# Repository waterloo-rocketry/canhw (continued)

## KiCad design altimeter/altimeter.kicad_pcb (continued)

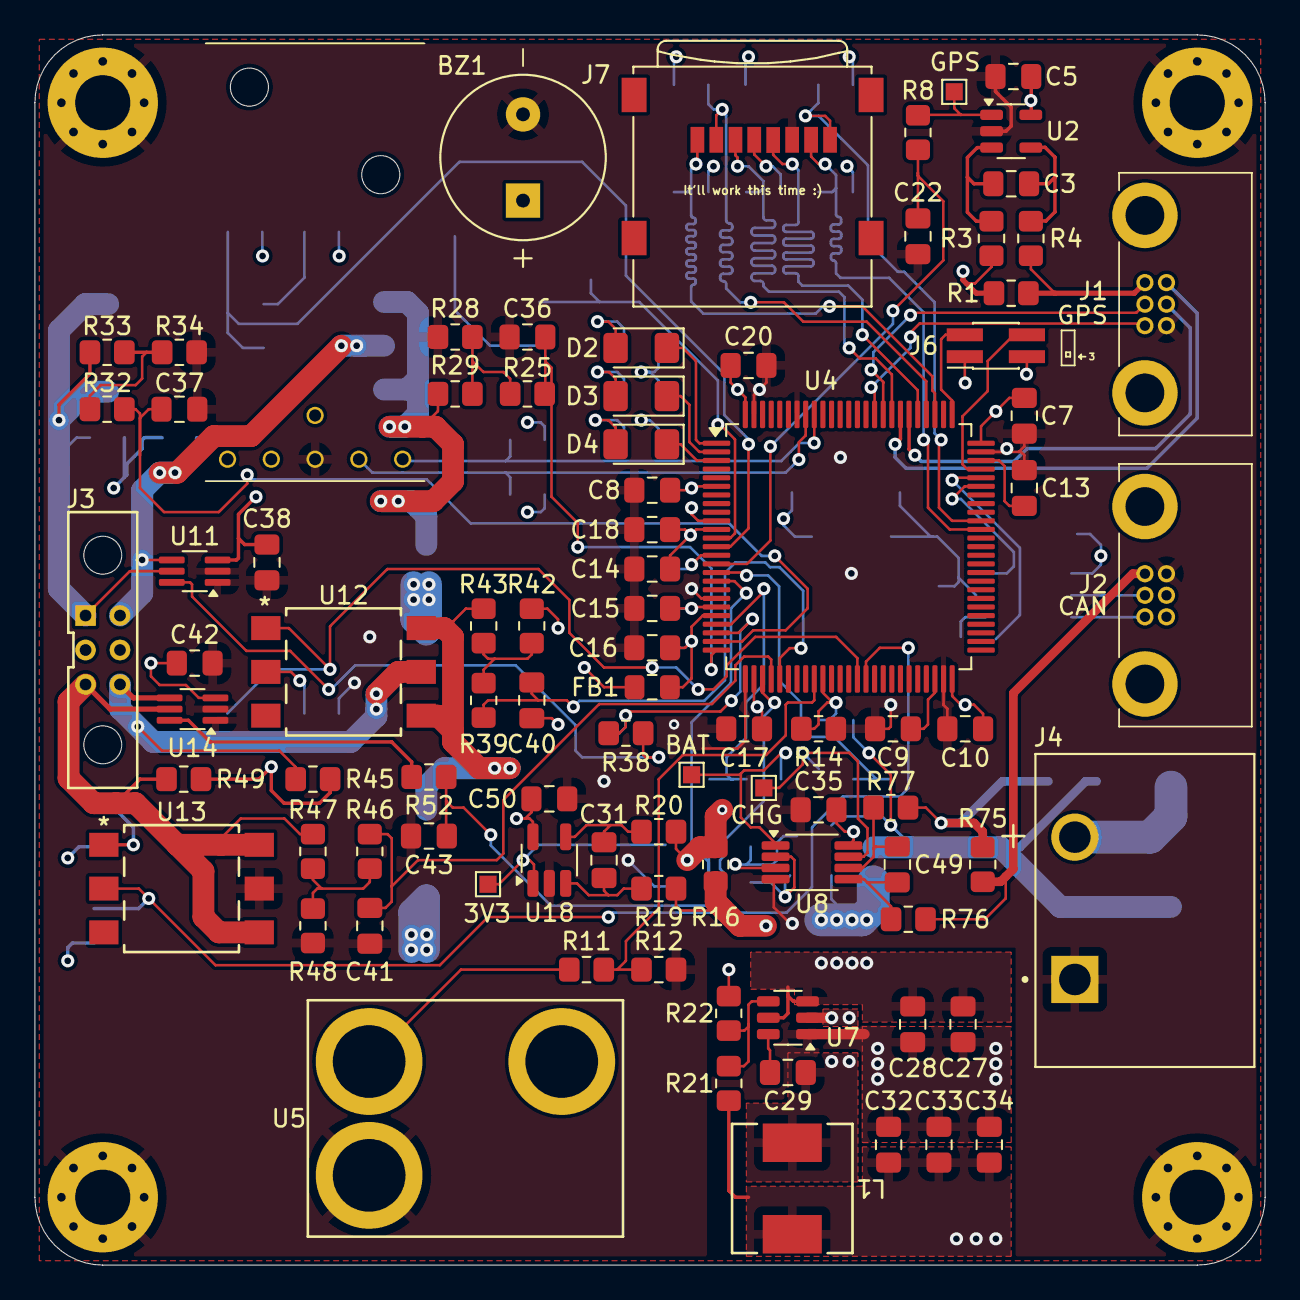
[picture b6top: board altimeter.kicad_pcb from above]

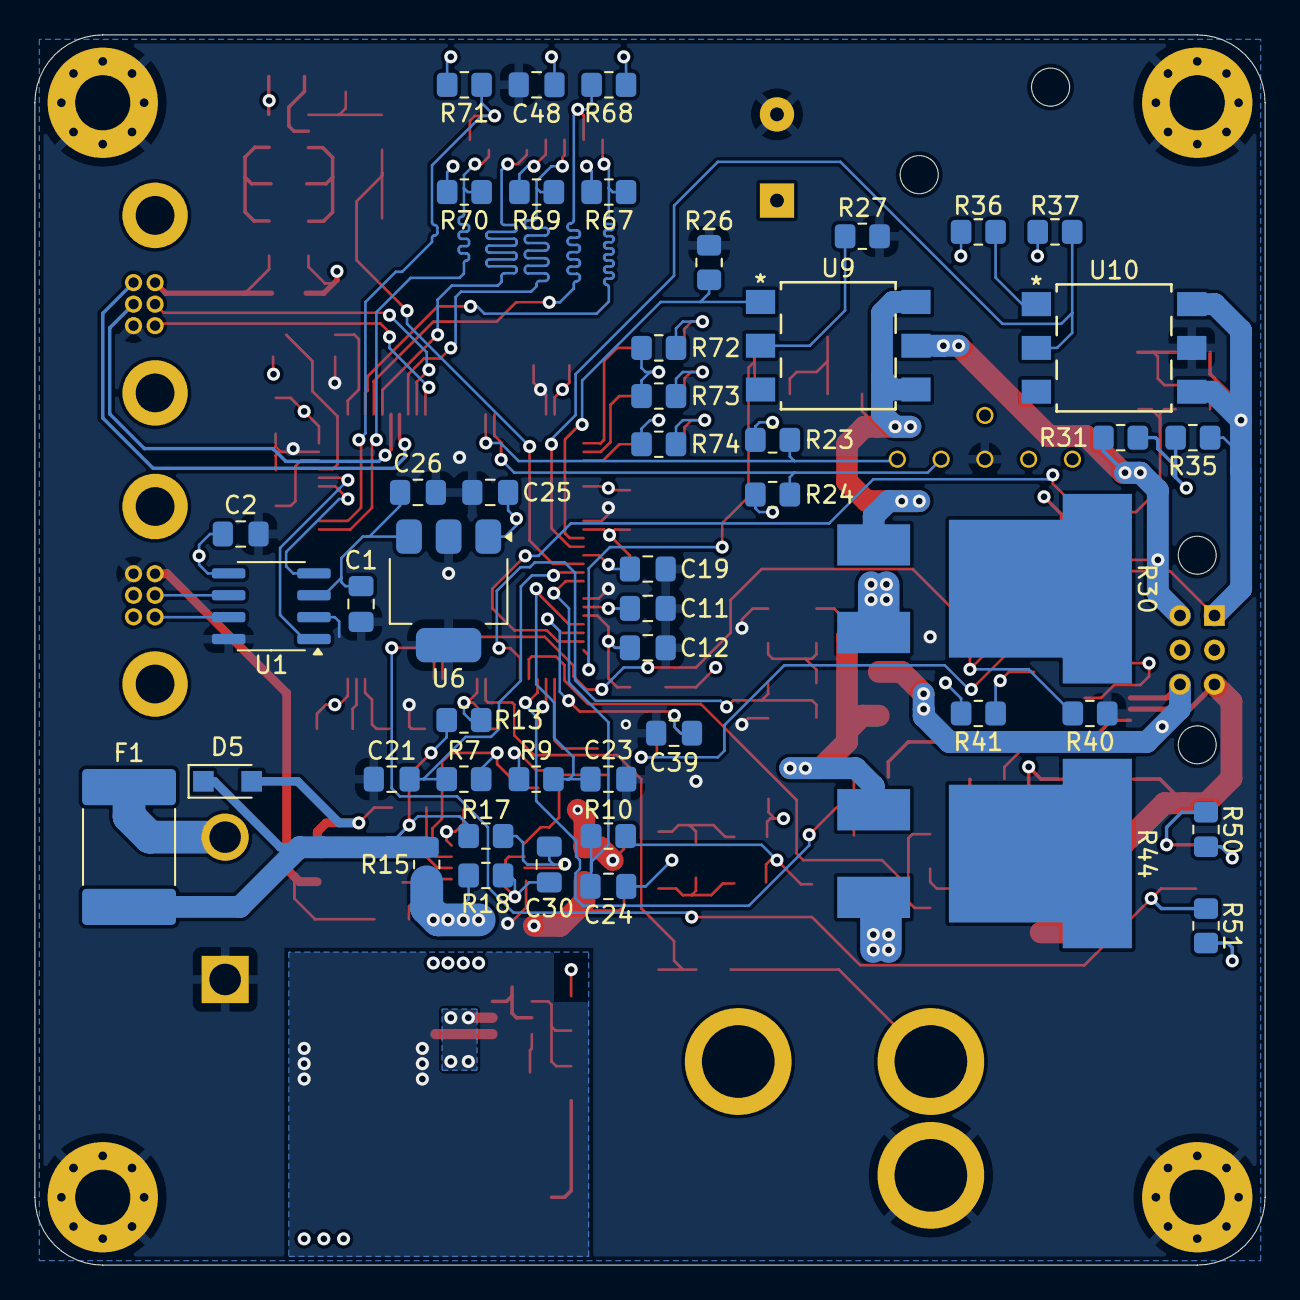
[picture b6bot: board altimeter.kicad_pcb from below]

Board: 4 copper layers, 71.4 x 71.4 mm, 141 parts (48 on the bottom side), 87 nets.

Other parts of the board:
J5: Pololu; PololuAltIMUv6
J7: Micro_SD_Card; microSD_Molex_WM6698CT-ND
R67, R68, R69, R70, R71: 10kR; R_0805_2012Metric_Pad1.20x1.40mm_HandSolder
R72, R73, R74: 100R; R_0805_2012Metric_Pad1.20x1.40mm_HandSolder

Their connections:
/mcu/SDMMC1_CK: J7.5 (CLK); also elsewhere on the board
/mcu/SDMMC1_CMD: J7.3 (CMD), R69.2; also elsewhere on the board
/mcu/SDMMC1_D0: J7.7 (DAT0), R70.2; also elsewhere on the board
/mcu/SDMMC1_D1: J7.8 (DAT1), R71.2; also elsewhere on the board
/mcu/SDMMC1_D2: J7.1 (DAT2), R67.2; also elsewhere on the board
/mcu/SDMMC1_D3: J7.2 (DAT3/CD), R68.2; also elsewhere on the board
GND: J5.4, J7.6 (VSS); also elsewhere on the board
unnamed 56: R72.1; also elsewhere on the board
unnamed 57: R73.1; also elsewhere on the board
unnamed 58: R74.1; also elsewhere on the board

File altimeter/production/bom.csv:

Designator,Footprint,Quantity,Value,LCSC Part #
3V3,TestPoint_Pad_1.0x1.0mm,1,BATT_CURR,
BZ1,CUI_CMI-9605-1280T,1,CMI-9605-1280T,
"C1, C2, C27, C28, C35, C38, C42, C5, C50",0805,9,10uF,
"C10, C11, C12, C17, C18, C20, C29, C7, C8",0805,9,100nF,
"C13, C9",0805,2,2.2uF,
"C14, C48",0805,2,4.7uF,
"C15, C16, C3, C30, C31, C49",0805,6,1uF,
C19,0805,1,0.1uF,
"C21, C22, C23, C24, C36, C37, C39, C40, C41, C43",0805,10,47nF,
C25,0805,1,0.33uF,
C26,0805,1,0.22uF,
"C32, C33, C34",0805,3,22uF,
CHG,TestPoint_Pad_1.0x1.0mm,1,CHG_CURR,
D2,1206,1,YELLOW,
D3,1206,1,RED,
D4,1206,1,GREEN,
D5,Nexperia_CFP3_SOD-123W,1,"PMEG2010ER,115",
F1,2920,1,2920L700/24SLER,
FB1,0805,1,BLM21PG221SN1D,
"H1, H2, H3, H4",MountingHole_3.2mm_M3_Pad_Via,4,MountingHole_Pad,
J1,connector_Harwin_G125–MG10605M4P,1,GPS,
J2,connector_Harwin_G125–MG10605M4P,1,RocketCAN,
J3,connector_Harwin_M80-5000642,1,M80-5000642,
J4,TE_2-1437667-4,1,4DB-P108-02,
J5,PololuAltIMUv6,1,Pololu,
J6,PinSocket_2x02_P1.27mm_Vertical_SMD,1,Programmer,
J7,microSD_Molex_WM6698CT-ND,1,Micro_SD_Card,
L1,IND_IHLP-2525CZ_VIS,1,IHLP2525CZER2R2M11,
R1,0805,1,0.02R,
"R10, R25, R32, R38, R39, R46, R52, R7, R8, R9",0805,10,5k,
"R11, R13, R29, R43",0805,4,60k,
"R12, R14, R28, R31, R35, R42, R45, R49",0805,8,20k,
R15,0805,1,0.002R,
R16,0805,1,0.01R,
"R17, R18, R19, R20, R3, R4, R76, R77",0805,8,10R,
R21,0805,1,33.2k,
"R22, R23, R24, R26, R37, R40, R51",0805,7,10k,
"R27, R36, R41, R50",0805,4,250R,
"R30, R44",RES_PWR263S_BRN,2,PWR263S-35-5R00F,
"R33, R47",0805,2,1.5k,
"R34, R48",0805,2,500R,
"R67, R68, R69, R70, R71",0805,5,10kR,
"R72, R73, R74",0805,3,100R,
R75,0805,1,0.015R,
TP2,TestPoint_Pad_1.0x1.0mm,1,GPS_CURR,
TP4,TestPoint_Pad_1.0x1.0mm,1,3V3_CURR,
U1,SOIC-8_3.9x4.9mm_P1.27mm,1,MCP2562,
"U10, U12, U13, U9",TLP3543A__6P4X7P12_TOS,4,TLP3543A,
"U11, U14",SOT-363_SC-70-6_Handsoldering,2,INA210AIDCKT,
U18,SOT-23-5_HandSoldering,1,INA180A4,
U2,SOT-23-5,1,INA180A4,
U4,LQFP-100_14x14mm_P0.5mm,1,STM32H750VBTx,
U5,Mag Switch,1,Mag Switch,
U6,SOT-223,1,NCV33275ST5.0T3G,
U7,SOT-23-6,1,TPS563200DDCR,
U8,VSSOP-8_3x3mm_P0.65mm,1,INA2180A4IDGKR,

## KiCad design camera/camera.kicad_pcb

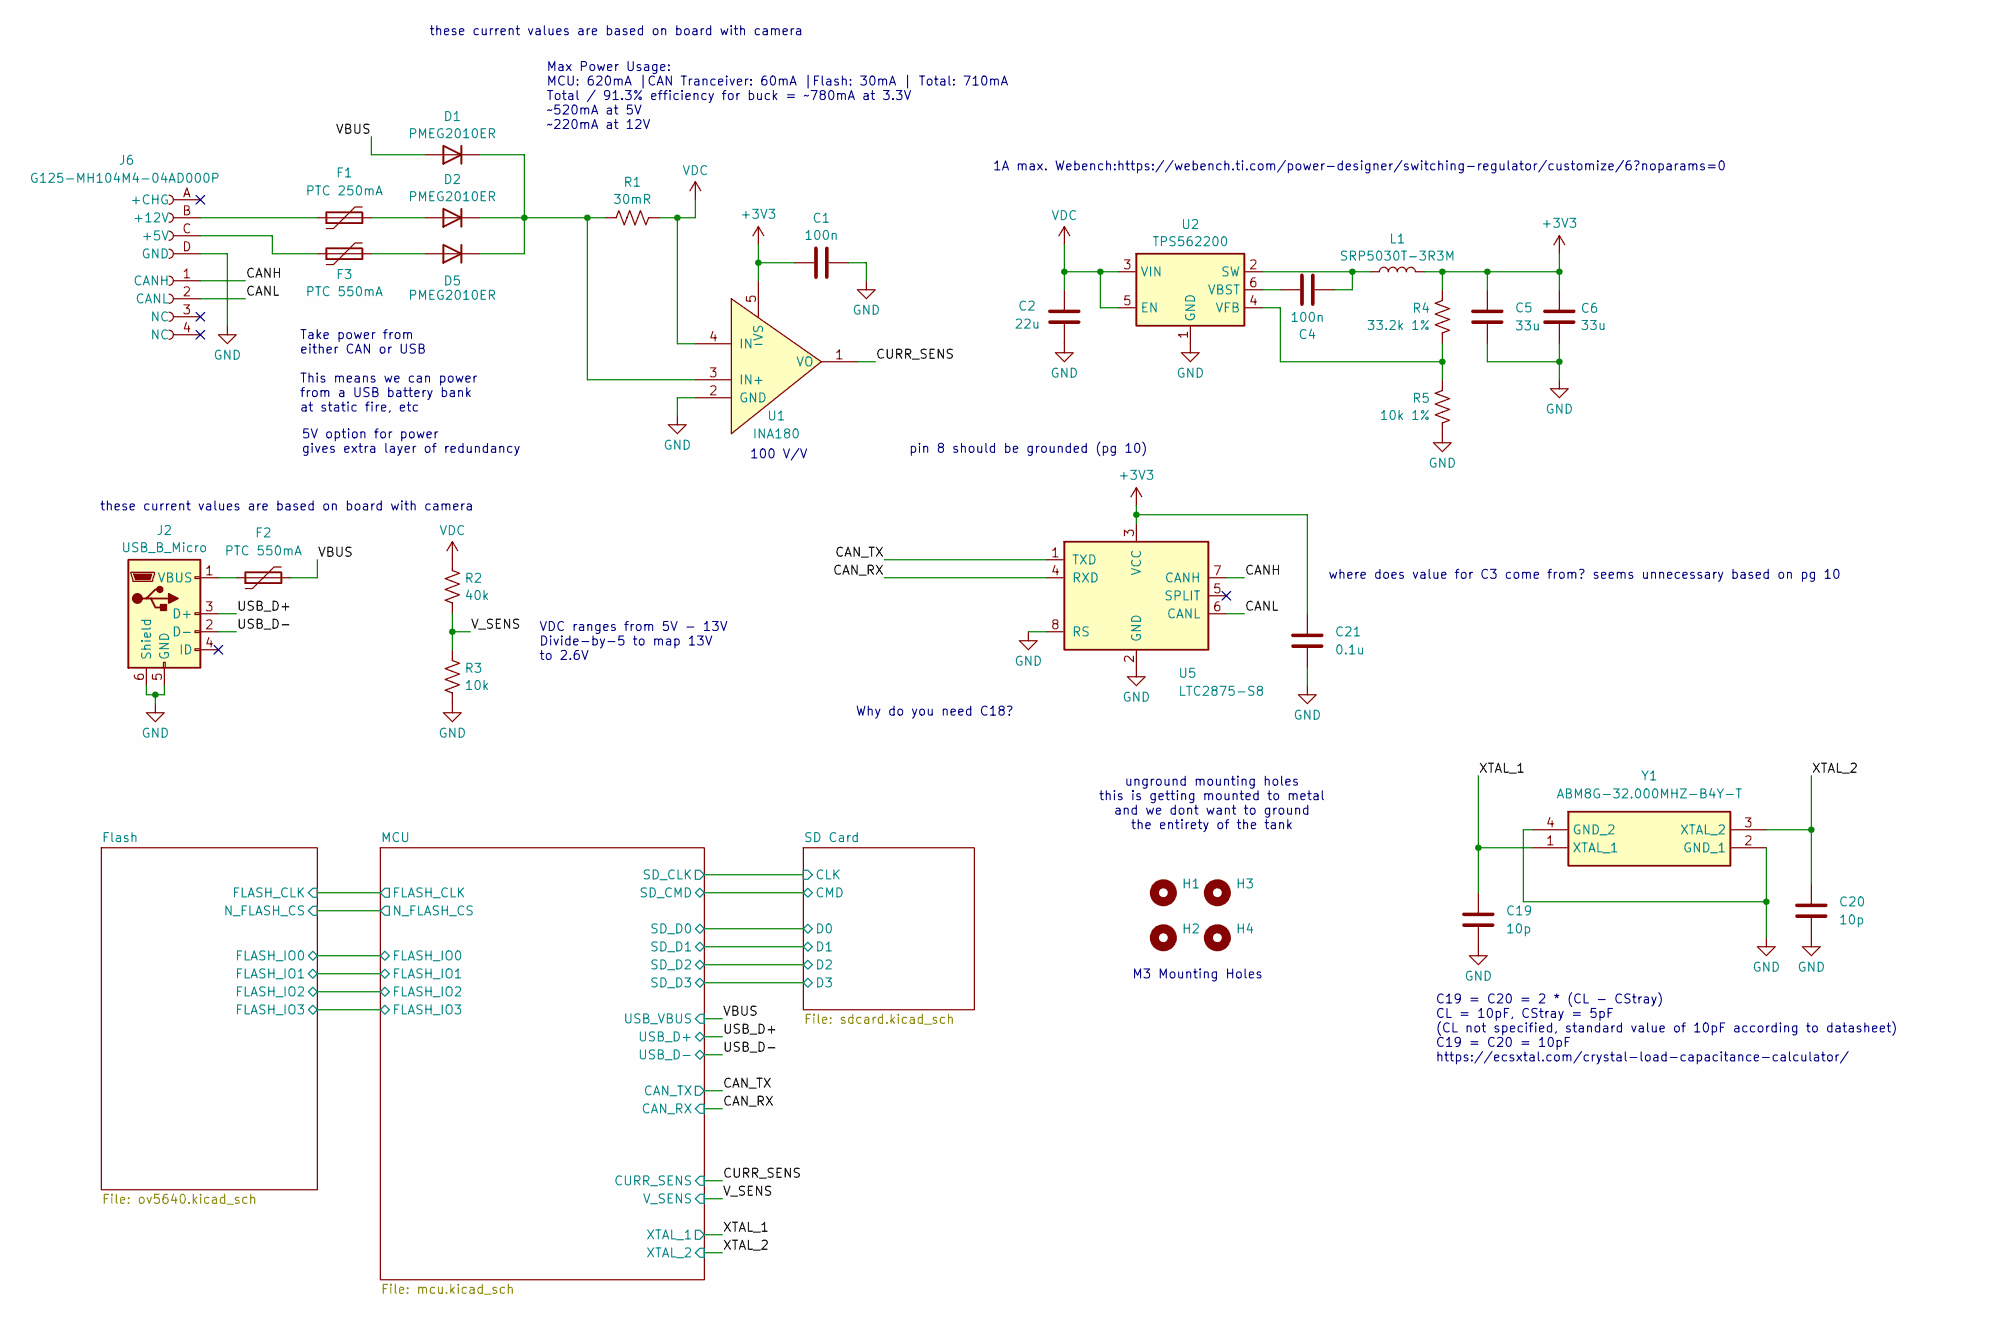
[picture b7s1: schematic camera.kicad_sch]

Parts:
C1, C4: 100n; C_0603_1608Metric_Pad1.08x0.95mm_HandSolder
C2: 22u; C_0603_1608Metric_Pad1.08x0.95mm_HandSolder
C5, C6: 33u; C_0603_1608Metric_Pad1.08x0.95mm_HandSolder
C19, C20: 10p; C_0603_1608Metric_Pad1.08x0.95mm_HandSolder
C21: 0.1u; C_0603_1608Metric_Pad1.08x0.95mm_HandSolder
D1, D2, D5: PMEG2010ER; Nexperia_CFP3_SOD-123W
F1: PTC 250mA; Fuse_1206_3216Metric_Pad1.42x1.75mm_HandSolder
F2, F3: PTC 550mA; Fuse_1206_3216Metric_Pad1.42x1.75mm_HandSolder
H1, H2, H3, H4: MountingHole; MountingHole_3.2mm_M3
J2: USB_B_Micro; USB_Micro-B_Molex_47346-0001
J6: G125-MH104M4-04AD000P; connector_Harwin_G125-MH104M4-04AD000P
L1: SRP5030T-3R3M; L_Bourns_SRP5030T
R1: 30mR; R_0603_1608Metric_Pad0.98x0.95mm_HandSolder
R2: 40k; R_0603_1608Metric_Pad0.98x0.95mm_HandSolder
R3: 10k; R_0603_1608Metric_Pad0.98x0.95mm_HandSolder
R4: 33.2k 1%; R_0603_1608Metric_Pad0.98x0.95mm_HandSolder
R5: 10k 1%; R_0603_1608Metric_Pad0.98x0.95mm_HandSolder
U1: INA180; SOT-23-5_HandSoldering
U2: TPS562200; SOT-23-6_Handsoldering
U5: LTC2875-S8; SOIC-8_3.9x4.9mm_P1.27mm
Y1: ABM8G-32.000MHZ-B4Y-T; Crystal_SMD_Abracon_ABM8G-4Pin_3.2x2.5mm; Manufacturer_Part_Number ABM8G-32.000MHZ-B4Y-T

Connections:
/CANH: J6.1 (CANH), U5.7 (CANH)
/CANL: J6.2 (CANL), U5.6 (CANL)
/CAN_RX: U5.4 (RXD); also elsewhere on the board
/CAN_TX: U5.1 (TXD); also elsewhere on the board
/CURR_SENS: U1.1 (VO); also elsewhere on the board
/USB_D+: J2.3 (D+); also elsewhere on the board
/USB_D-: J2.2 (D-); also elsewhere on the board
/VBUS: D1.2 (A), F2.2; also elsewhere on the board
/V_SENS: R2.2, R3.1; also elsewhere on the board
/XTAL_1: C19.1, Y1.1 (XTAL_1); also elsewhere on the board
/XTAL_2: C20.1, Y1.3 (XTAL_2); also elsewhere on the board
GND: C1.2, C2.2, C5.2, C6.2, C19.2, C20.2, C21.2, J2.5 (GND), J2.6 (Shield), J6.D (GND), R3.2, R5.2, U1.2 (GND), U2.1 (GND), U5.2 (GND), U5.8 (RS), Y1.2 (GND_1), Y1.4 (GND_2); also elsewhere on the board
unnamed: D1.1 (K), D2.1 (K), D5.1 (K), R1.1, U1.3 (IN+)
unnamed: D2.2 (A), F1.2
unnamed: D5.2 (A), F3.2
unnamed: F2.1, J2.1 (VBUS)
unnamed: F3.1, J6.C (+5V)
unnamed: F1.1, J6.B (+12V)
unnamed: C4.2, L1.1, U2.2 (SW)
unnamed: C4.1, U2.6 (VBST)
unnamed: R4.2, R5.1, U2.4 (VFB)
VDC: C2.1, R1.2, R2.1, U1.4 (IN-), U2.3 (VIN), U2.5 (EN)

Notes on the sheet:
unground mounting holes this is getting mounted to metal and we dont want to ground the entirety of the tank
5V option for power gives extra layer of redundancy
pin 8 should be grounded (pg 10)
C19 = C20 = 2 * (CL - CStray) CL = 10pF, CStray = 5pF (CL not specified, standard value of 10pF according to datasheet) C19 = C20 = 10pF https://ecsxtal.com/crystal-load-capacitance-calculator/
VDC ranges from 5V - 13V Divide-by-5 to map 13V to 2.6V
these current values are based on board with camera
100 V/V
Why do you need C18?
1A max. Webench:https://webench.ti.com/power-designer/switching-regulator/customize/6?noparams=0
M3 Mounting Holes
Max Power Usage: MCU: 620mA |CAN Tranceiver: 60mA |Flash: 30mA | Total: 710mA Total / 91.3% efficiency for buck = ~780mA at 3.3V ~520mA at 5V ~220mA at 12V
where does value for C3 come from? seems unnecessary based on pg 10
Take power from either CAN or USB This means we can power from a USB battery bank at static fire, etc

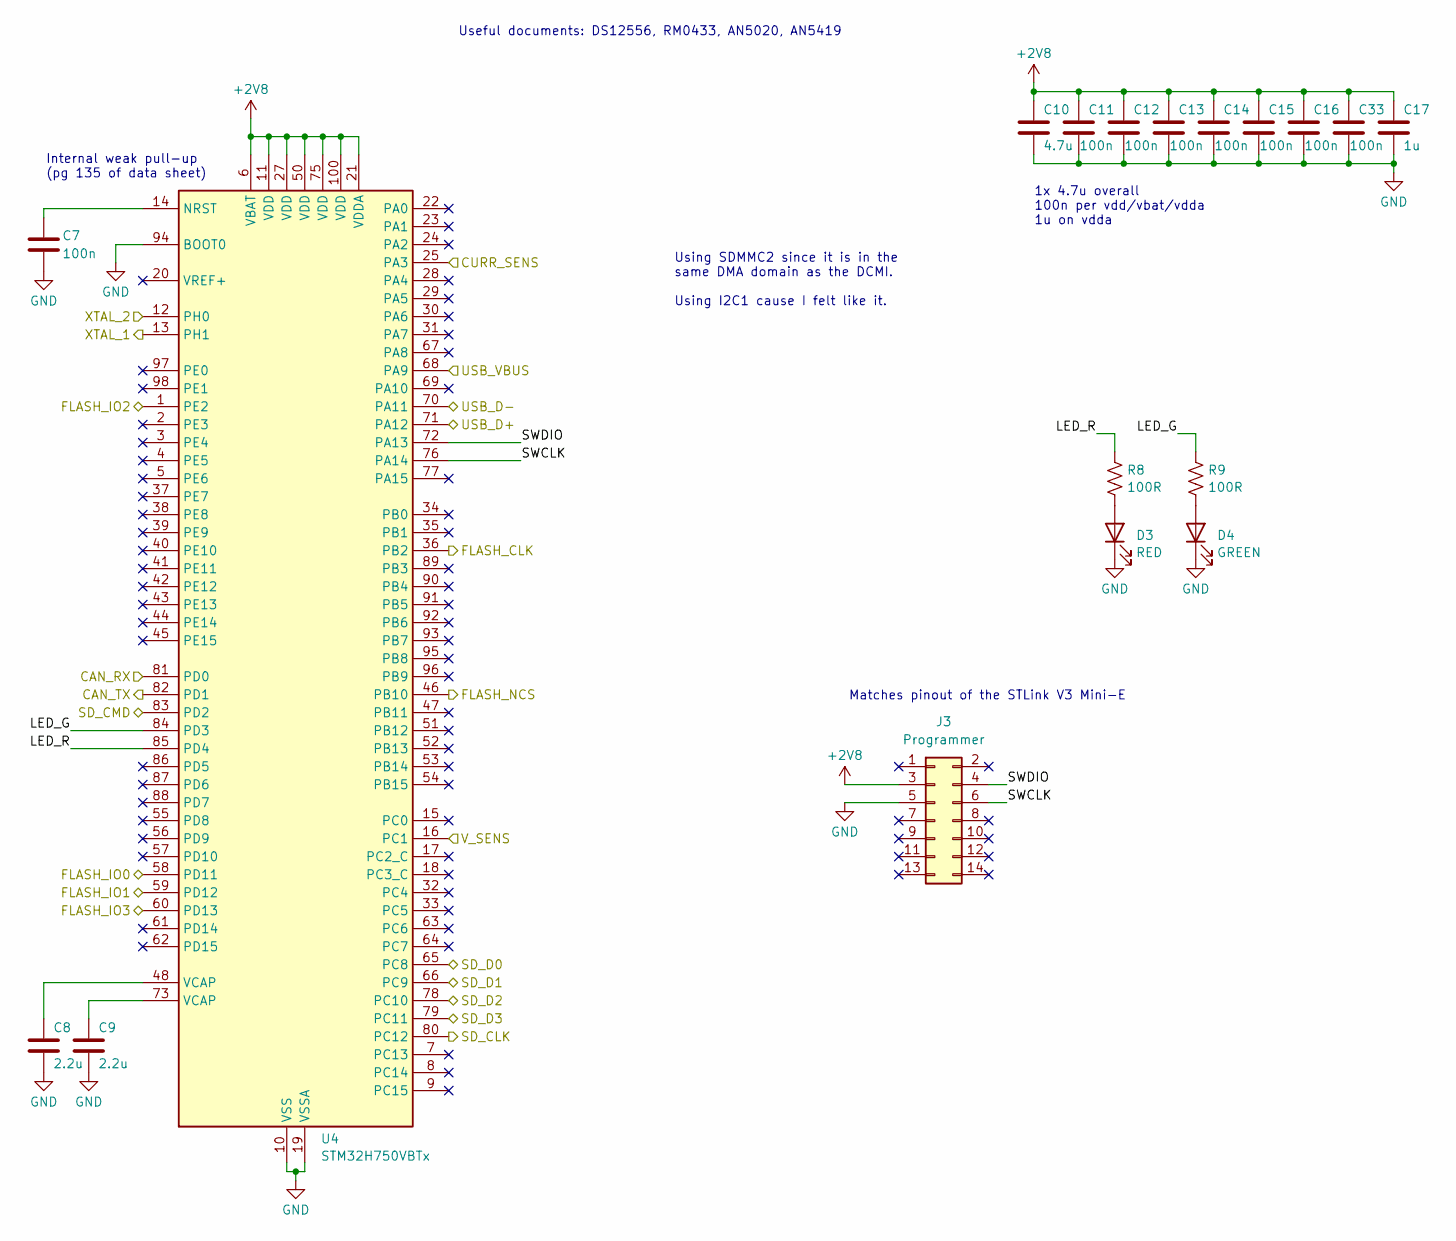
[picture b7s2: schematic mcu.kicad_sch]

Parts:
C7, C11, C12, C13, C14, C15, C16, C33: 100n; C_0603_1608Metric_Pad1.08x0.95mm_HandSolder
C8, C9: 2.2u; C_0603_1608Metric_Pad1.08x0.95mm_HandSolder
C10: 4.7u; C_0603_1608Metric_Pad1.08x0.95mm_HandSolder
C17: 1u; C_0603_1608Metric_Pad1.08x0.95mm_HandSolder
D3: RED; LED_1206_3216Metric_Pad1.42x1.75mm_HandSolder
D4: GREEN; LED_1206_3216Metric_Pad1.42x1.75mm_HandSolder
J3: Programmer; PinHeader_2x07_P1.27mm_Vertical_SMD
R8, R9: 100R; R_0603_1608Metric_Pad0.98x0.95mm_HandSolder
U4: STM32H750VBTx; LQFP-100_14x14mm_P0.5mm

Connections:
/CAN_RX: U4.81 (PD0); also elsewhere on the board
/CAN_TX: U4.82 (PD1); also elsewhere on the board
/CURR_SENS: U4.25 (PA3); also elsewhere on the board
/Flash/FLASH_CLK: U4.36 (PB2); also elsewhere on the board
/Flash/FLASH_IO0: U4.58 (PD11); also elsewhere on the board
/Flash/FLASH_IO1: U4.59 (PD12); also elsewhere on the board
/Flash/FLASH_IO2: U4.1 (PE2); also elsewhere on the board
/Flash/FLASH_IO3: U4.60 (PD13); also elsewhere on the board
/Flash/N_FLASH_CS: U4.46 (PB10); also elsewhere on the board
/MCU/LED_G: R9.1, U4.84 (PD3)
/MCU/LED_R: R8.1, U4.85 (PD4)
/MCU/SD_CLK: U4.80 (PC12); also elsewhere on the board
/MCU/SD_CMD: U4.83 (PD2); also elsewhere on the board
/MCU/SD_D0: U4.65 (PC8); also elsewhere on the board
/MCU/SD_D1: U4.66 (PC9); also elsewhere on the board
/MCU/SD_D2: U4.78 (PC10); also elsewhere on the board
/MCU/SD_D3: U4.79 (PC11); also elsewhere on the board
/MCU/SWCLK: J3.6, U4.76 (PA14)
/MCU/SWDIO: J3.4, U4.72 (PA13)
/USB_D+: U4.71 (PA12); also elsewhere on the board
/USB_D-: U4.70 (PA11); also elsewhere on the board
/VBUS: U4.68 (PA9); also elsewhere on the board
/V_SENS: U4.16 (PC1); also elsewhere on the board
/XTAL_1: U4.13 (PH1); also elsewhere on the board
/XTAL_2: U4.12 (PH0); also elsewhere on the board
GND: C7.2, C8.2, C9.2, C10.2, C11.2, C12.2, C13.2, C14.2, C15.2, C16.2, C17.2, C33.2, D3.1 (K), D4.1 (K), J3.5, U4.10 (VSS), U4.19 (VSSA), U4.26 (VSS), U4.49 (VSS), U4.74 (VSS), U4.94 (BOOT0), U4.99 (VSS); also elsewhere on the board
unnamed: C8.1, U4.48 (VCAP)
unnamed: C9.1, U4.73 (VCAP)
unnamed: D3.2 (A), R8.2
unnamed: D4.2 (A), R9.2
unnamed: C7.1, U4.14 (NRST)

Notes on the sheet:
1x 4.7u overall 100n per vdd/vbat/vdda 1u on vdda
Matches pinout of the STLink V3 Mini-E
Useful documents: DS12556, RM0433, AN5020, AN5419
Using SDMMC2 since it is in the same DMA domain as the DCMI. Using I2C1 cause I felt like it.
Internal weak pull-up (pg 135 of data sheet)

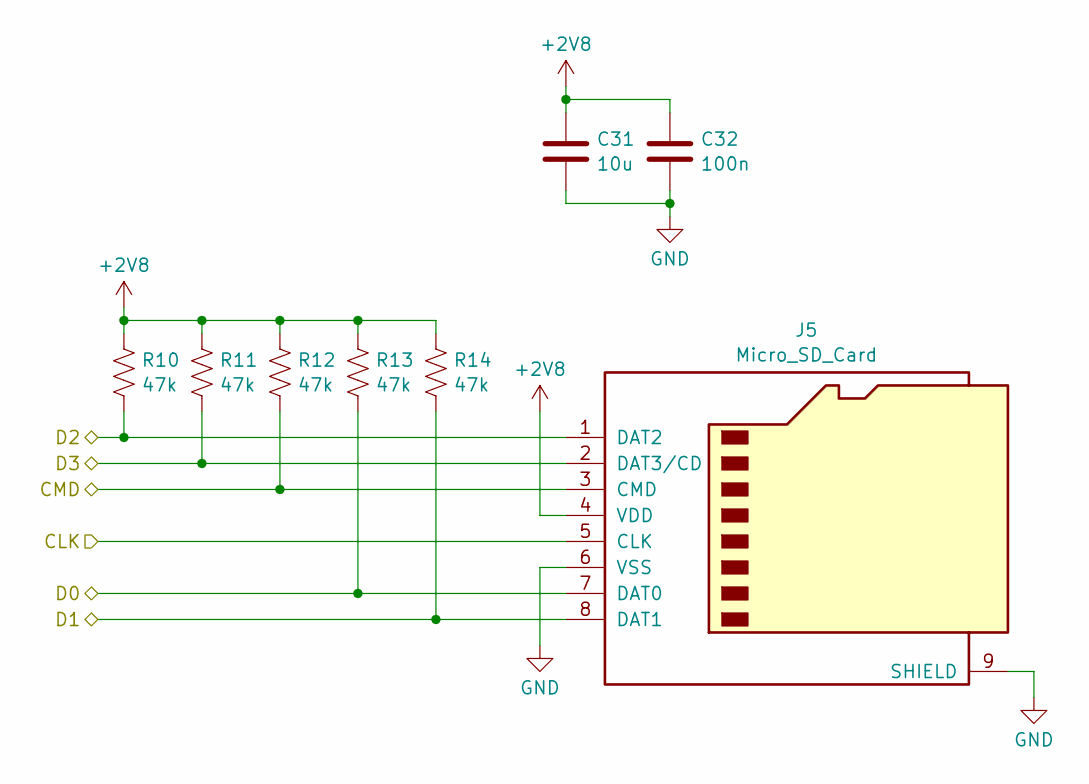
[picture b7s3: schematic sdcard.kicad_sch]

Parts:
C31: 10u; C_0603_1608Metric_Pad1.08x0.95mm_HandSolder
C32: 100n; C_0603_1608Metric_Pad1.08x0.95mm_HandSolder
J5: Micro_SD_Card; microSD_Molex_WM6698CT-ND
R10, R11, R12, R13, R14: 47k; R_0603_1608Metric_Pad0.98x0.95mm_HandSolder

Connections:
/MCU/SD_CLK: J5.5 (CLK); also elsewhere on the board
/MCU/SD_CMD: J5.3 (CMD), R12.2; also elsewhere on the board
/MCU/SD_D0: J5.7 (DAT0), R13.2; also elsewhere on the board
/MCU/SD_D1: J5.8 (DAT1), R14.2; also elsewhere on the board
/MCU/SD_D2: J5.1 (DAT2), R10.2; also elsewhere on the board
/MCU/SD_D3: J5.2 (DAT3/CD), R11.2; also elsewhere on the board
GND: C31.2, C32.2, J5.6 (VSS), J5.9 (SHIELD); also elsewhere on the board

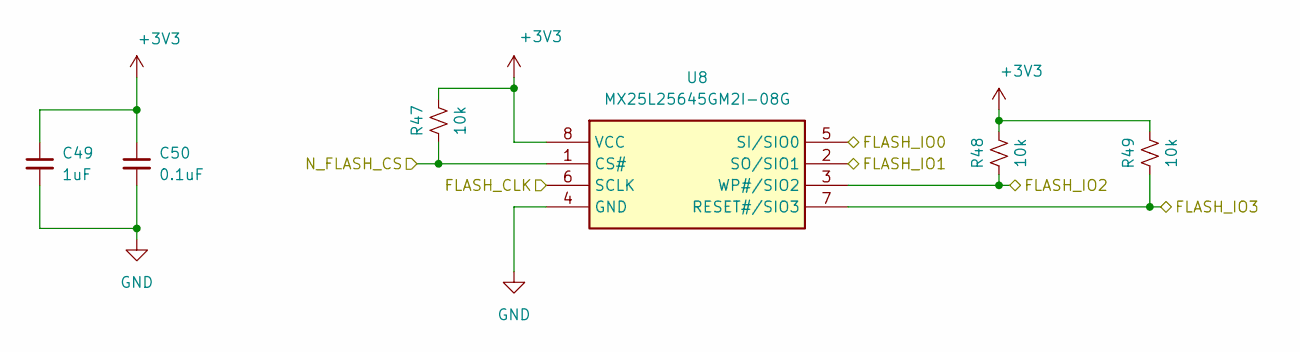
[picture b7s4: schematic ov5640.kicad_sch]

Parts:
C49: 1uF; C_0603_1608Metric_Pad1.08x0.95mm_HandSolder; LCSC Part # C49678
C50: 0.1uF; C_0603_1608Metric_Pad1.08x0.95mm_HandSolder; LCSC Part # C49678
R47, R48, R49: 10k; R_0603_1608Metric_Pad0.98x0.95mm_HandSolder; LCSC Part # C17414
U8: MX25L25645GM2I-08G; SOIC-8_5.3x5.3mm_P1.27mm; Mouser Part Number 95-25L25645GM2I0TR

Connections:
/Flash/FLASH_CLK: U8.6 (SCLK); also elsewhere on the board
/Flash/FLASH_IO0: U8.5 (SI/SIO0); also elsewhere on the board
/Flash/FLASH_IO1: U8.2 (SO/SIO1); also elsewhere on the board
/Flash/FLASH_IO2: R48.2, U8.3 (WP#/SIO2); also elsewhere on the board
/Flash/FLASH_IO3: R49.2, U8.7 (RESET#/SIO3); also elsewhere on the board
/Flash/N_FLASH_CS: R47.2, U8.1 (CS#); also elsewhere on the board
GND: C49.2, C50.2, U8.4 (GND); also elsewhere on the board

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
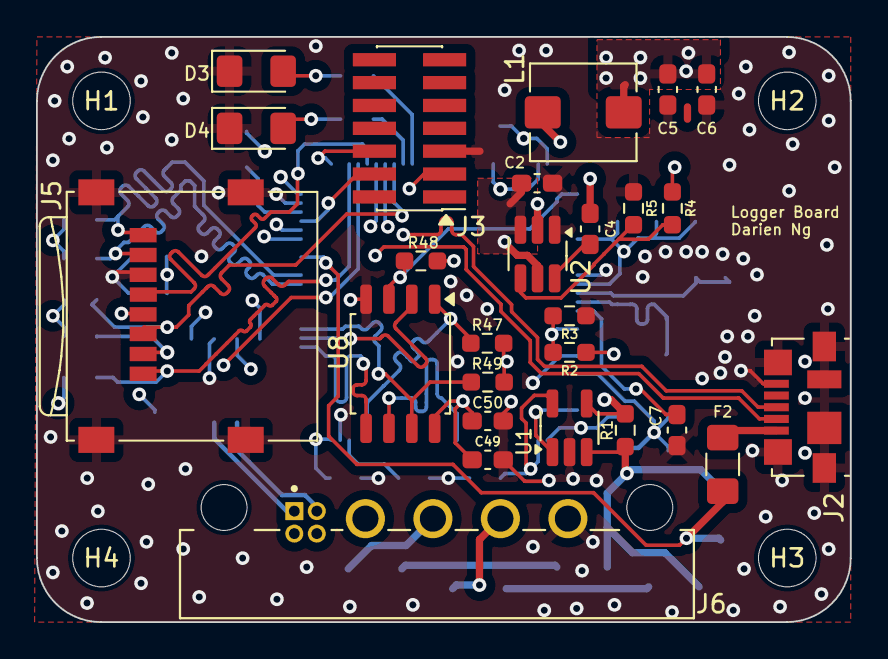
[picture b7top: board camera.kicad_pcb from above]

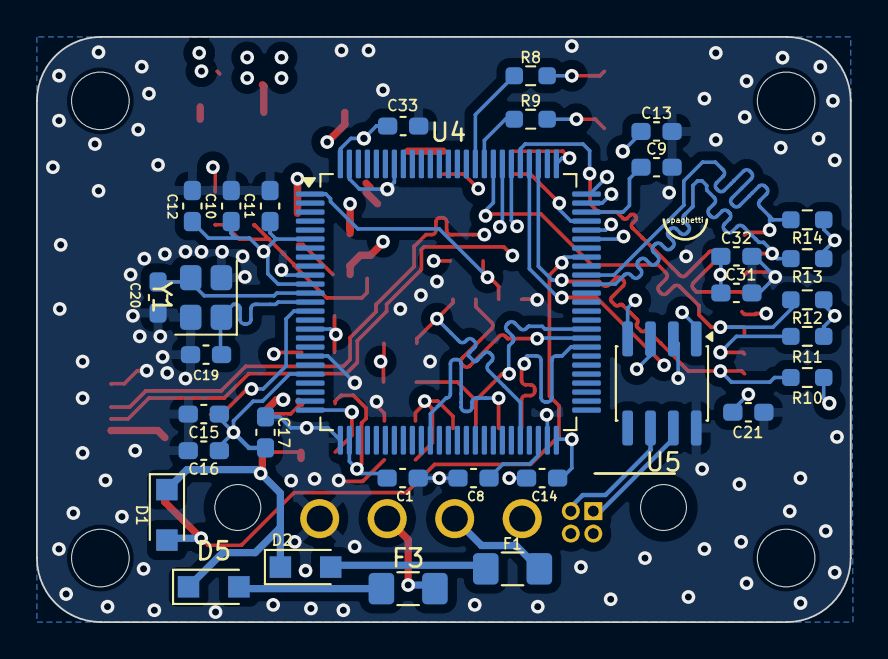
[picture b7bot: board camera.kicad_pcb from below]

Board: 4 copper layers, 45.2 x 32.5 mm, 62 parts (32 on the bottom side), 44 nets.

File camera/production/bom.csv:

Designator,Footprint,Quantity,Value,LCSC Part #
"C1, C11, C12, C13, C14, C15, C16, C32, C33, C4, C7",0603,11,100n,
C10,0603,1,4.7u,
C17,0603,1,1u,
"C18, C3",0603,2,0.1u,
"C19, C20",0603,2,10p,
C2,0603,1,22u,
C31,0603,1,10u,
C49,0603,1,1uF,C49678
"C5, C6",0603,2,33u,
C50,0603,1,0.1uF,C49678
"C8, C9",0603,2,2.2u,
"D1, D2",Nexperia_CFP3_SOD-123W,2,PMEG2010ER,
D3,1206,1,RED,
D4,1206,1,GREEN,
F1,1206,1,PTC 350mA,
F2,1206,1,PTC 750mA,
"H1, H2, H3, H4",MountingHole_3.2mm_M3_Pad,4,MountingHole_Pad,
J2,USB_Micro-B_Molex_47346-0001,1,USB_B_Micro,
J3,PinHeader_2x07_P1.27mm_Vertical_SMD,1,Programmer,
J5,microSD_Molex_WM6698CT-ND,1,Micro_SD_Card,
J6,connector_Harwin_G125-MH104M4-04AD000P,1,G125-MH104M4-04AD000P,
L1,L_Bourns_SRP5030T,1,SRP5030T-3R3M,
R1,0603,1,30mR,
"R10, R11, R12, R13, R14",0603,5,47k,
R2,0603,1,40k,
R3,0603,1,10k,
R4,0603,1,26.7k 1%,
"R47, R48, R49",0603,3,10k,C17414
R5,0603,1,10k 1%,
"R8, R9",0603,2,100R,
U1,SOT-23-5_HandSoldering,1,INA180,
U2,SOT-23-6,1,TPS562200,
U3,SOIC-8_3.9x4.9mm_P1.27mm,1,MCP2562,
U4,LQFP-100_14x14mm_P0.5mm,1,STM32H750VBTx,
U8,SOIC-8_5.3x5.3mm_P1.27mm,1,MX25L25645GM2I-08G,
Y1,Crystal_SMD_Abracon_ABM8AIG-4Pin_3.2x2.5mm,1,ABM8G-32.000MHZ-B4Y-T,
